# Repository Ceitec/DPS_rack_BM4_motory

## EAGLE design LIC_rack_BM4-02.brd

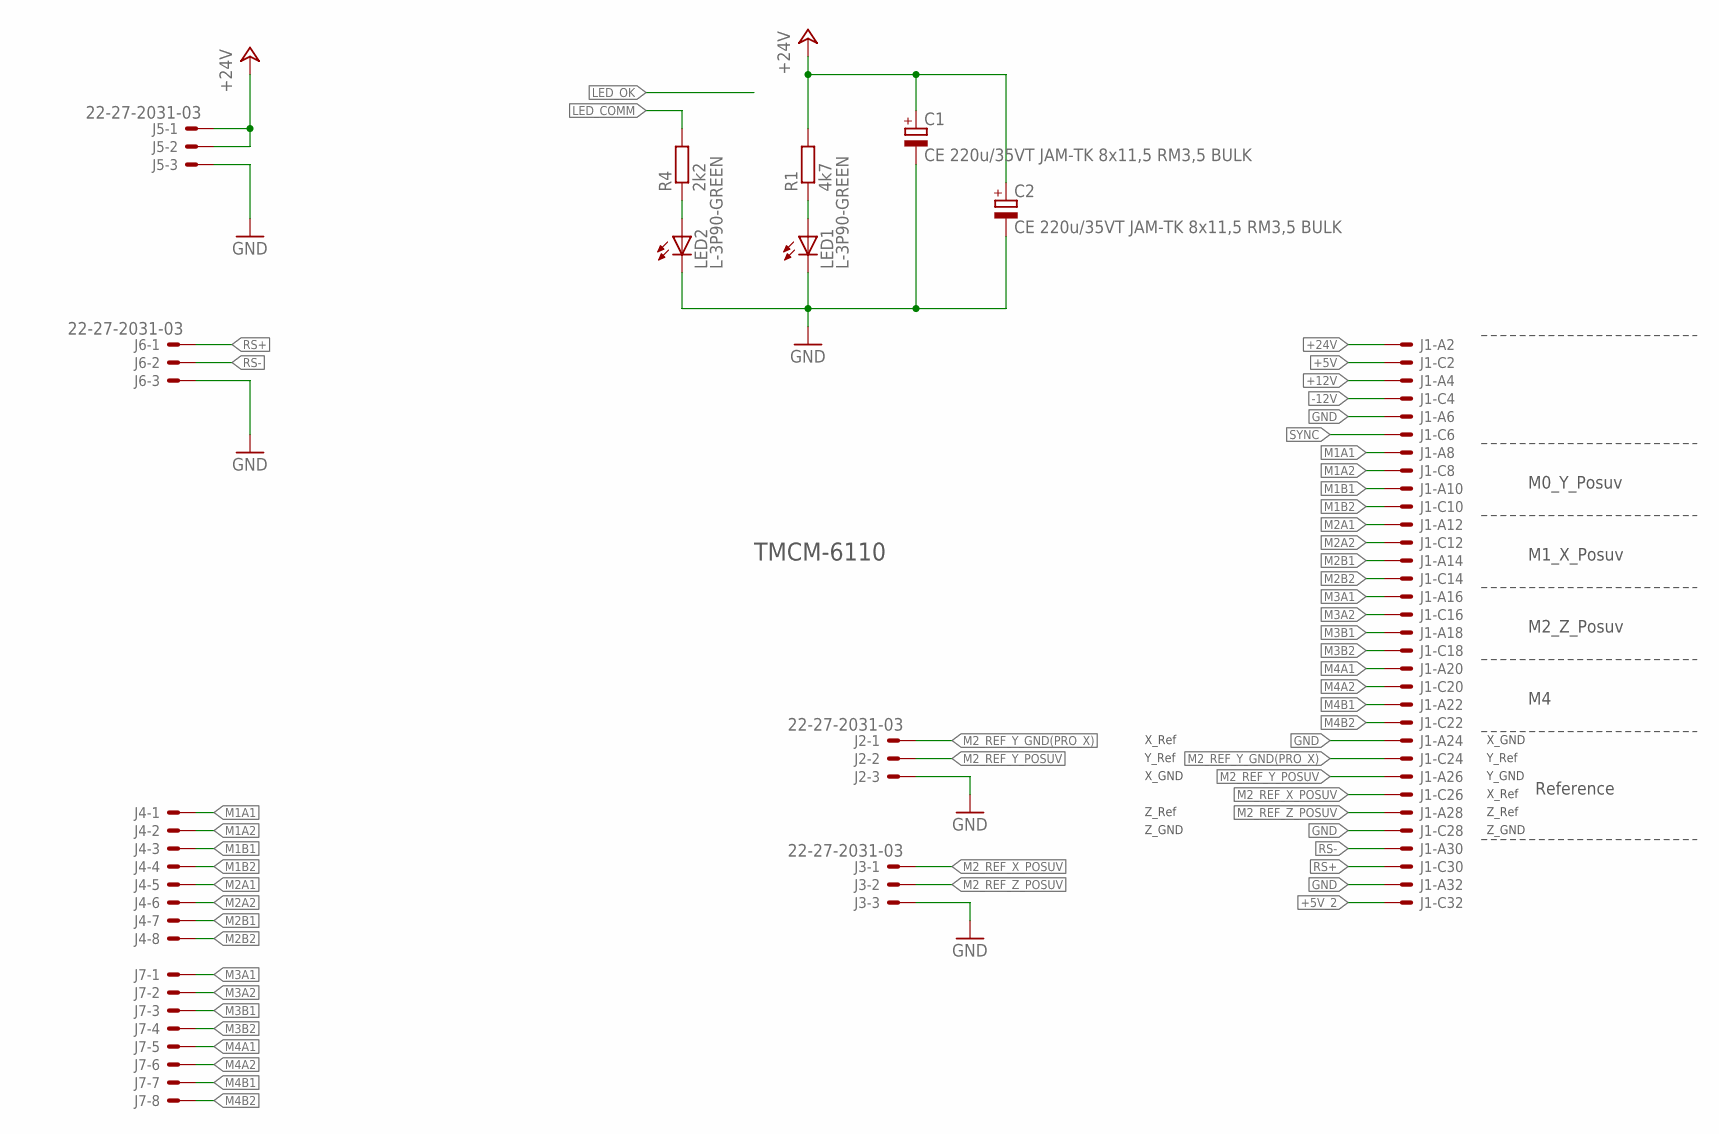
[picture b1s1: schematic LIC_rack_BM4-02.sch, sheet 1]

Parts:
C1, C2: CE 220u/35VT JAM-TK 8x11,5 RM3,5 BULK; E3,5-8L
J1: VG32SP; VG32P
J2, J3, J5, J6: 22-27-2031-03; 6410-03
J4, J7: 22-27-2081-08; 6410-08
LED1, LED2: L-3P90-GREEN; L-3P90
R1: 4k7; R1206
R4: 2k2; R1206

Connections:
+5V: J1.C2 (MS)
+5V_2: J1.C32 (MSV); also elsewhere on the board
+12V: J1.A4 (MS)
+24V: C1.+, C2.+, J1.A2 (MS), J5.1, J5.2, R1.2
-12V: J1.C4 (MS)
GND: C1.-, C2.-, J1.A6 (MS), J1.A24 (MS), J1.A32 (MS), J1.C28 (MS), J2.3, J3.3, J5.3, J6.3, LED1.K (C), LED2.K (C); also elsewhere on the board
LED_COMM: R4.2; also elsewhere on the board
M1A1: J1.A8 (MS), J4.1
M1A2: J1.C8 (MS), J4.2
M1B1: J1.A10 (MS), J4.3
M1B2: J1.C10 (MS), J4.4
M2A1: J1.A12 (MS), J4.5
M2A2: J1.C12 (MS), J4.6
M2B1: J1.A14 (MS), J4.7
M2B2: J1.C14 (MS), J4.8
M2_REF_X_POSUV: J1.C26 (MS), J3.1
M2_REF_Y_GND(PRO_X): J1.C24 (MS), J2.1
M2_REF_Y_POSUV: J1.A26 (MS), J2.2
M2_REF_Z_POSUV: J1.A28 (MS), J3.2
M3A1: J1.A16 (MS), J7.1
M3A2: J1.C16 (MS), J7.2
M3B1: J1.A18 (MS), J7.3
M3B2: J1.C18 (MS), J7.4
M4A1: J1.A20 (MS), J7.5
M4A2: J1.C20 (MS), J7.6
M4B1: J1.A22 (MS), J7.7
M4B2: J1.C22 (MS), J7.8
unnamed: LED1.A, R1.1
unnamed: LED2.A, R4.1
RS+: J1.C30 (MS), J6.1; also elsewhere on the board
RS-: J1.A30 (MS), J6.2; also elsewhere on the board
SYNC: J1.C6 (MS)

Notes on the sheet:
TMCM-6110
M0_Y_Posuv
M1_X_Posuv
M2_Z_Posuv
Reference
X_Ref
Y_Ref
Z_Ref
X_GND
Y_GND
Z_GND

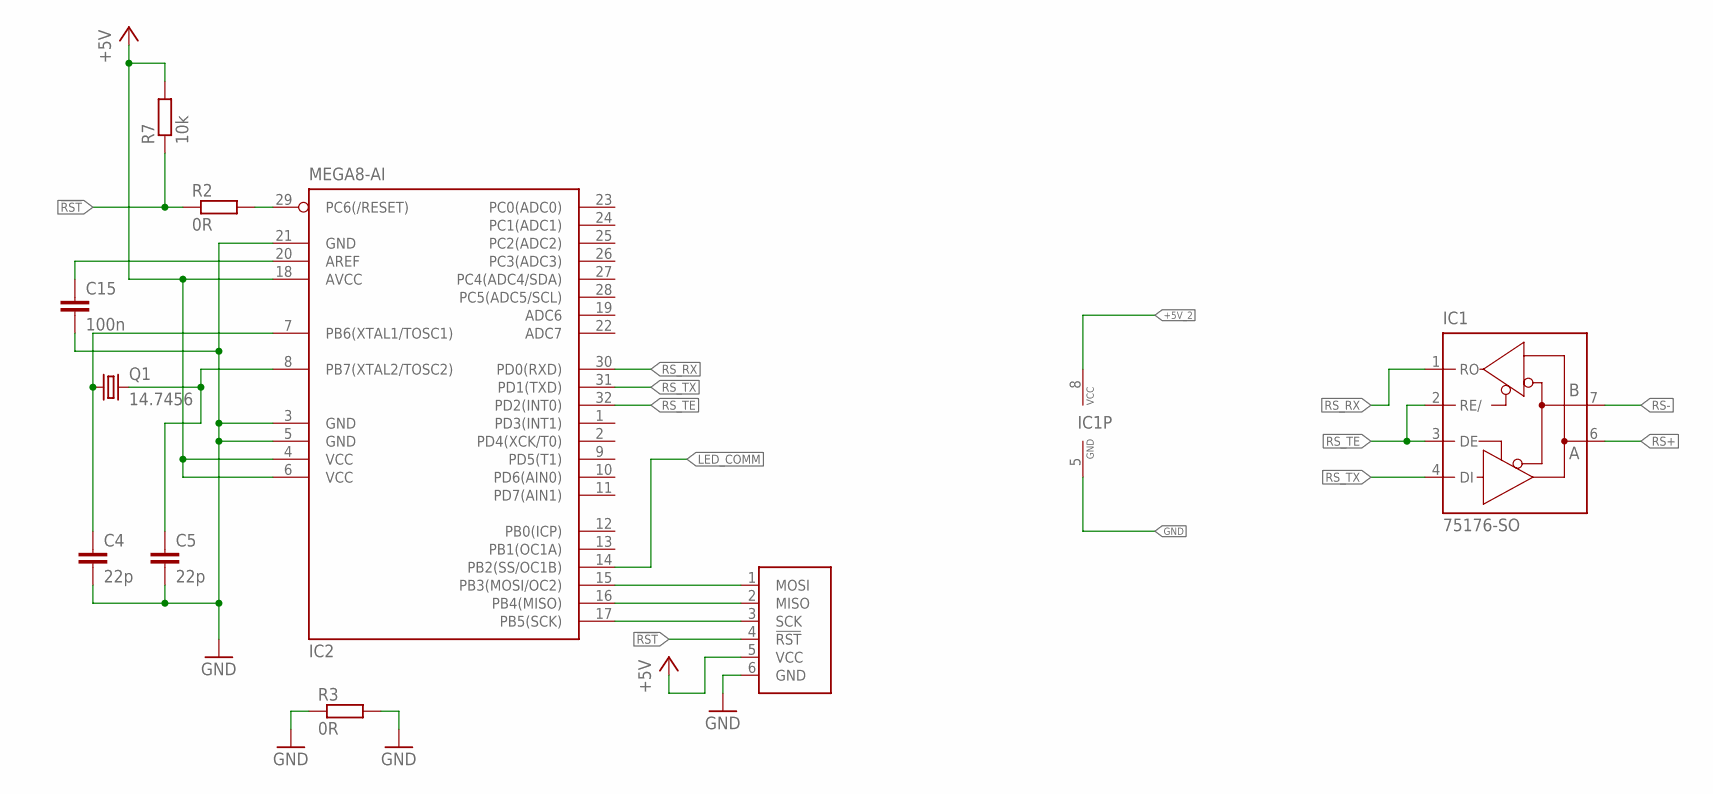
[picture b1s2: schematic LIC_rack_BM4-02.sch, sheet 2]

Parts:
C4, C5: 22p; C0805
C15: 100n; C1206
IC1: 75176-SO; SO08
IC2: MEGA8-AI; TQFP32-08
Q1: 14.7456; HC49U70
R2, R3: 0R; R1206
R7: 10k; R1206
U1: ATPROG-V; 6410-06

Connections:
!RST: R2.1, R7.1, U1.4 (!RST)
+5V_2: IC1.8 (VCC), IC2.4 (VCC), IC2.6 (VCC), IC2.18 (AVCC), R7.2, U1.5 (VCC); also elsewhere on the board
AREF: C15.1, IC2.20 (AREF)
GND: C4.2, C5.2, C15.2, IC1.5 (GND), IC2.3 (GND), IC2.5 (GND), IC2.21 (GND), R3.1, R3.2, U1.6 (GND); also elsewhere on the board
LED_COMM: IC2.14 (PB2(SS/OC1B)); also elsewhere on the board
unnamed: IC2.29 (PC6(/RESET)), R2.2
PROG_MISO: IC2.16 (PB4(MISO)), U1.2 (MISO)
PROG_MOSI: IC2.15 (PB3(MOSI/OC2)), U1.1 (MOSI)
PROG_SCK: IC2.17 (PB5(SCK)), U1.3 (SCK)
RS+: IC1.6 (A); also elsewhere on the board
RS-: IC1.7 (B); also elsewhere on the board
RS_RX: IC1.1 (RO), IC2.30 (PD0(RXD))
RS_TE: IC1.2 (RE/), IC1.3 (DE), IC2.32 (PD2(INT0))
RS_TX: IC1.4 (DI), IC2.31 (PD1(TXD))
XTAL1: C4.1, IC2.7 (PB6(XTAL1/TOSC1)), Q1.1
XTAL2: C5.1, IC2.8 (PB7(XTAL2/TOSC2)), Q1.2

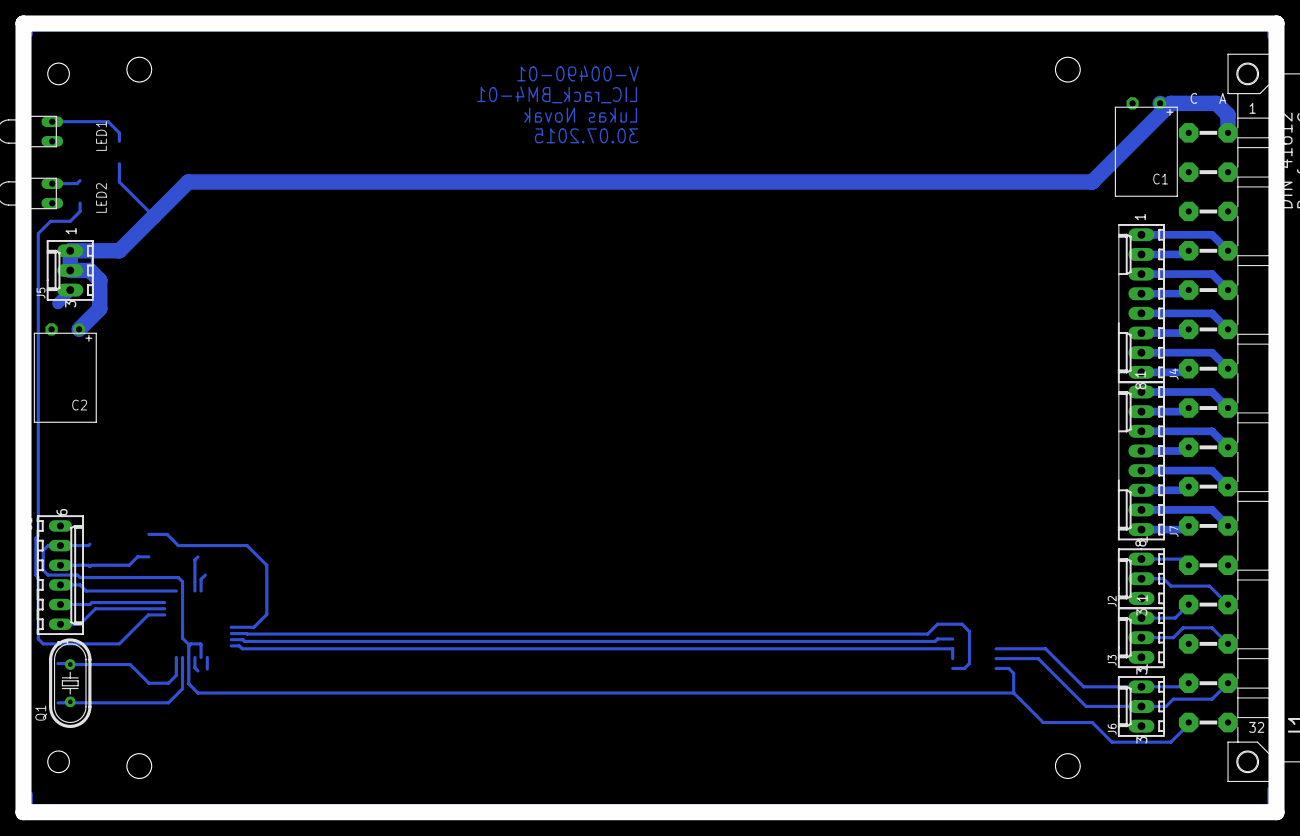
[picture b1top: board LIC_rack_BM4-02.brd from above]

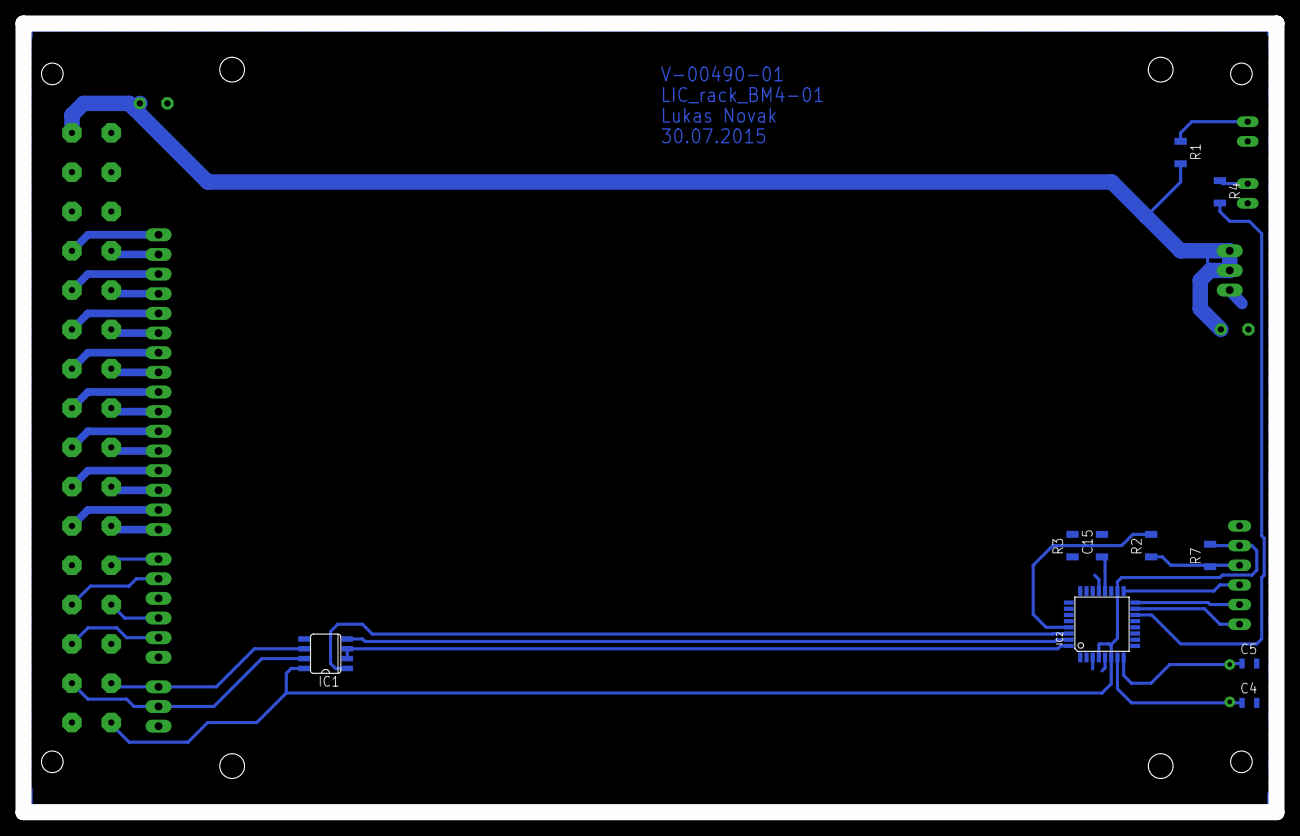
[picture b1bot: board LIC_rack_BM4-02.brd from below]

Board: 2 copper layers, 162.0 x 102.0 mm, 23 parts (10 on the bottom side), 39 nets.

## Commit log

2015-08-11 :boom::camel: Added .gitattributes & .gitignore files
2015-08-11 Ovládání motorů
2015-08-11 Pridani zakazanych koncovek
2015-09-25 A
    A
